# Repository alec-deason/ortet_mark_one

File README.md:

This is the electronics design and firmware for the Ortet Mark One MIDI controller.

## How to flash the firmware

In order to flash the firmware on the the controller's RP Pico you'll need to setup your rust environment by installing the `thumbv6m-none-eabi` target:
```
rustup target add thumbv6m-none-eabi
```

Then you will need `elf2uf2-rs` for building the UF2:
```
cargo install elf2uf2-rs
```

Then put the Pico into bootloader mode by holding the BOOTSEL button on the board while plugging it in to your computer. The board should mount as a USB drive at which point you can run:
```
cargo run --release
```

The project should build and install itself onto the Pico, then the Pico should reboot and present as a USB MIDI device named `Ortet MIDI Controller`.

For more information see the rp_pico documentation: https://github.com/rp-rs/rp-hal-boards/tree/main/boards/rp-pico

## License

This work is licensed under either of

- Apache License, Version 2.0 ([LICENSE-APACHE](LICENSE-APACHE) or
  <http://www.apache.org/licenses/LICENSE-2.0>)
- MIT license ([LICENSE-MIT](LICENSE-MIT) or <http://opensource.org/licenses/MIT>)

at your option.

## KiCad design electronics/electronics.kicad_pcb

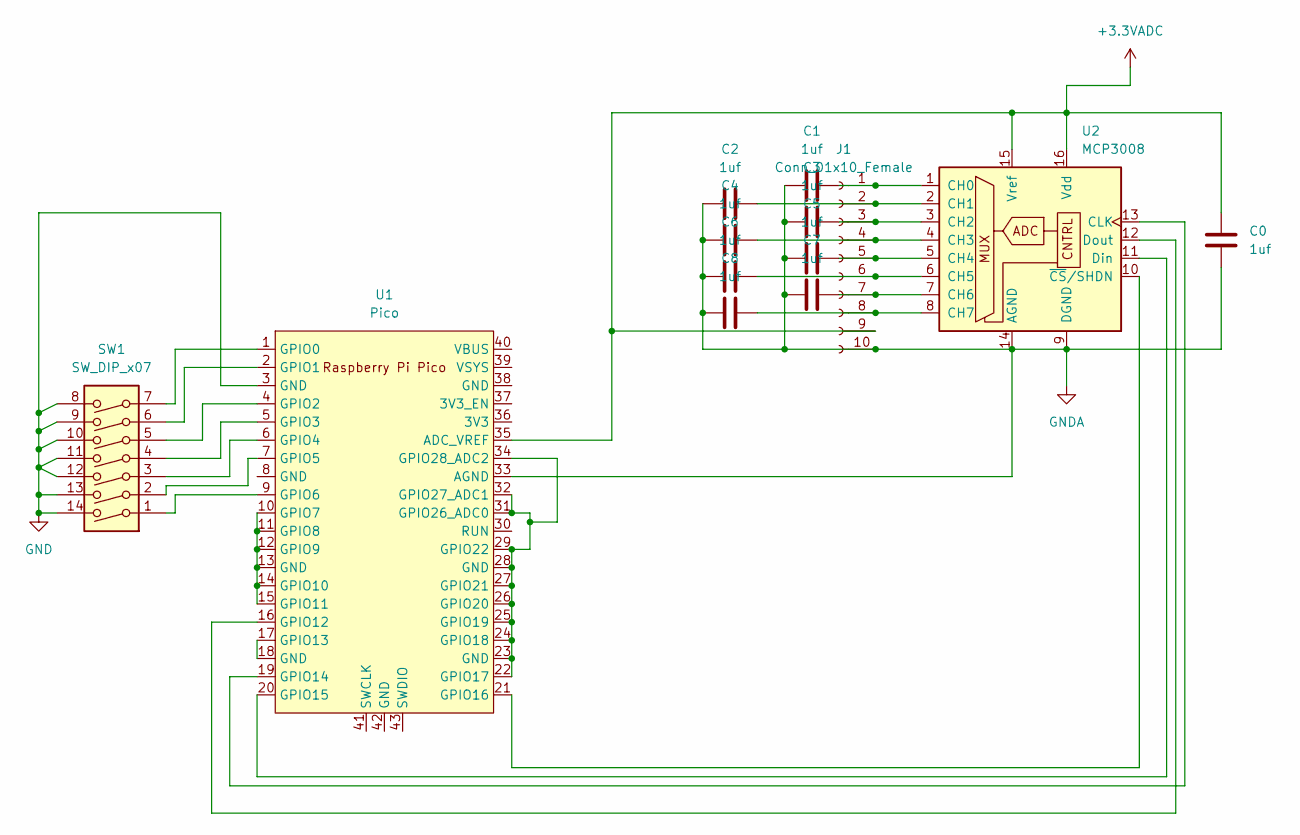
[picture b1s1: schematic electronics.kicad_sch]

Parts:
C0, C1, C2, C3, C4, C5, C6, C7, C8: 1uf; C_0603_1608Metric
J1: Conn_01x10_Female; PinHeader_2x05_P2.54mm_Vertical_SMD
SW1: SW_DIP_x07; DIP-14_W7.62mm_SMDSocket_SmallPads
U1: Pico; RPi_Pico_SMD_TH
U2: MCP3008; SOIC-16_3.9x9.9mm_P1.27mm

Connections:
+3.3VADC: C0.1, J1.9, U1.35 (ADC_VREF), U2.15 (Vref), U2.16 (Vdd)
GND: SW1.8, SW1.9, SW1.10, SW1.11, SW1.12, SW1.13, SW1.14, U1.3 (GND)
GNDA: C0.2, C1.1, C2.1, C3.1, C4.1, C5.1, C6.1, C7.1, C8.1, J1.10, U1.33 (AGND), U2.9 (DGND), U2.14 (AGND)
unnamed: C1.2, J1.1, U2.1 (CH0)
unnamed: C2.2, J1.2, U2.2 (CH1)
unnamed: C3.2, J1.3, U2.3 (CH2)
unnamed: C4.2, J1.4, U2.4 (CH3)
unnamed: C5.2, J1.5, U2.5 (CH4)
unnamed: C6.2, J1.6, U2.6 (CH5)
unnamed: C7.2, J1.7, U2.7 (CH6)
unnamed: C8.2, J1.8, U2.8 (CH7)
unnamed: SW1.1, U1.9 (GPIO6)
unnamed: SW1.2, U1.7 (GPIO5)
unnamed: SW1.3, U1.6 (GPIO4)
unnamed: SW1.4, U1.5 (GPIO3)
unnamed: SW1.5, U1.4 (GPIO2)
unnamed: SW1.6, U1.2 (GPIO1)
unnamed: SW1.7, U1.1 (GPIO0)
unnamed: U1.10 (GPIO7), U1.11 (GPIO8), U1.12 (GPIO9), U1.13 (GND), U1.14 (GPIO10), U1.15 (GPIO11)
unnamed: U1.16 (GPIO12), U2.12 (Dout)
unnamed: U1.17 (GPIO13), U1.18 (GND)
unnamed: U1.19 (GPIO14), U2.13 (CLK)
unnamed: U1.20 (GPIO15), U2.11 (Din)
unnamed: U1.21 (GPIO16), U2.10 (~CS/SHDN)
unnamed: U1.22 (GPIO17), U1.23 (GND), U1.24 (GPIO18), U1.25 (GPIO19), U1.26 (GPIO20), U1.27 (GPIO21), U1.28 (GND), U1.29 (GPIO22), U1.31 (GPIO26_ADC0), U1.32 (GPIO27_ADC1), U1.34 (GPIO28_ADC2)

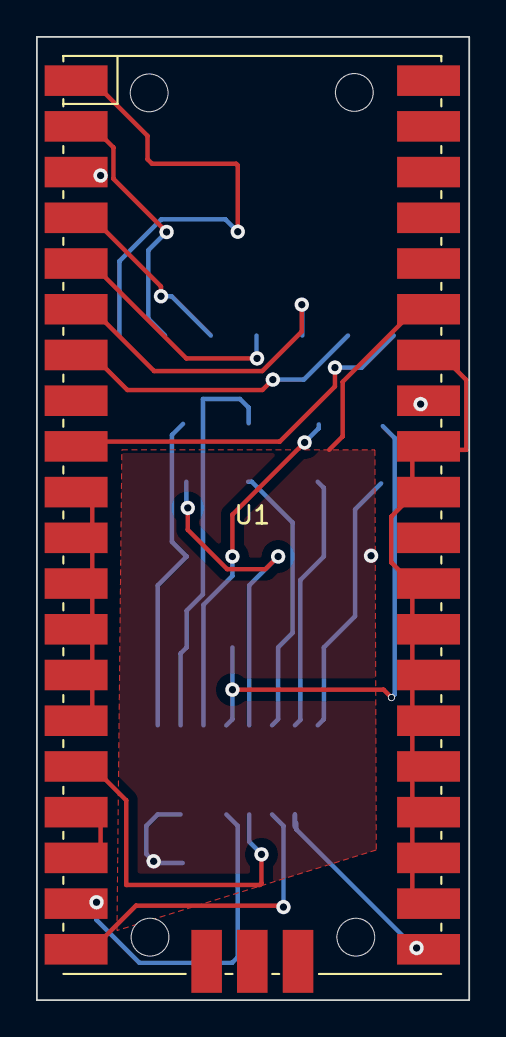
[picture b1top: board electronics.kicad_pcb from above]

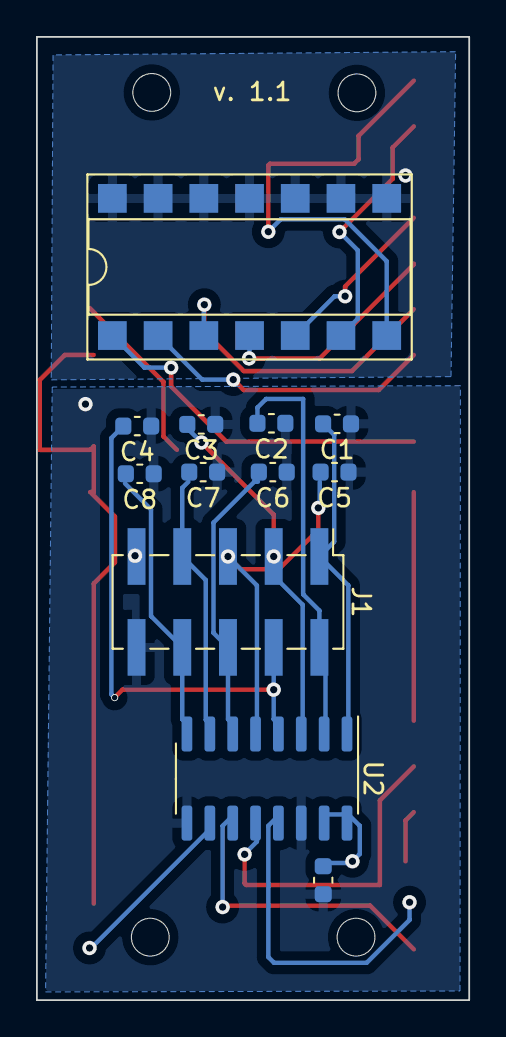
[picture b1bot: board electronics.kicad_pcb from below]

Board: 2 copper layers, 24.0 x 53.5 mm, 13 parts (12 on the bottom side), 25 nets.

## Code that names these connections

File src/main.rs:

//! Firmware for the Ortet Mark One series of midi controllers.

#![deny(warnings)]
#![no_std]
#![no_main]

use adc_mcp3008::Mcp3008;
use embedded_hal::digital::v2::{InputPin, OutputPin};
use fugit::RateExtU32;
use panic_halt as _;
use rp2040_hal::usb::UsbBus;
use rp_pico::entry;
use rp_pico::hal::{self, gpio::pin::bank0::Gpio16, pac, prelude::*};
use usb_device::{class_prelude::UsbBusAllocator, device::UsbVidPid, prelude::UsbDeviceBuilder};
use usbd_midi::{
    data::{
        byte::{from_traits::FromClamped, u7::U7},
        midi::{
            channel::Channel,
            message::{control_function::ControlFunction, Message},
        },
        usb::constants::USB_AUDIO_CLASS,
        usb_midi::{cable_number::CableNumber, usb_midi_event_packet::UsbMidiEventPacket},
    },
    midi_device::MidiClass,
};

type SPI = rp2040_hal::Spi<rp2040_hal::spi::Enabled, pac::SPI1, 8>;
type CS = rp2040_hal::gpio::Pin<Gpio16, rp2040_hal::gpio::Output<rp2040_hal::gpio::PushPull>>;

struct Controller {
    knob_values: [[u8; 2]; 8],

    midi_channel: Channel,
}

impl Controller {
    fn new(midi_channel: Channel) -> Self {
        Controller {
            knob_values: [[0,0]; 8],
            midi_channel,
        }
    }

    fn process_knobs(&mut self, adc: &mut Mcp3008<SPI, CS>, midi: &mut MidiClass<UsbBus>) -> Result<(), ()> {
        for i in 0..4 {
            let channel = match i {
                0 => adc_mcp3008::Channels8::CH0,
                1 => adc_mcp3008::Channels8::CH1,
                2 => adc_mcp3008::Channels8::CH2,
                3 => adc_mcp3008::Channels8::CH3,
                4 => adc_mcp3008::Channels8::CH4,
                5 => adc_mcp3008::Channels8::CH5,
                6 => adc_mcp3008::Channels8::CH6,
                7 => adc_mcp3008::Channels8::CH7,
                _ => unreachable!(),
            };
            let r = adc.read_channel(channel).map_err(|_| ())?;
            let r1 = (r / 8) as u8;
            if r1 != self.knob_values[i][0] && r1 != self.knob_values[i][1] {
                // We keep two samples worth of history here because sometimes there is just enough noise
                // to cause the value to bounce repeatedly between two adjacent values and we want to
                // suppress that without reducing over all sensitivity.
                self.knob_values[i][1] = self.knob_values[i][0];
                self.knob_values[i][0] = r1;
                let midi_message = UsbMidiEventPacket::from_midi(
                    CableNumber::Cable0,
                    Message::ControlChange(
                        self.midi_channel,
                        ControlFunction(U7::from_clamped(i as u8)),
                        U7::from_clamped(r1),
                    ),
                );
                midi.send_message(midi_message).map_err(|_| ())?;
            }
        }
        Ok(())
    }

    fn process(&mut self, adc: &mut Mcp3008<SPI, CS>, midi: &mut MidiClass<UsbBus>) -> Result<(), ()> {
        self.process_knobs(adc, midi)
    }
}

#[entry]
fn main() -> ! {
    let mut pac = pac::Peripherals::take().unwrap();
    let core = pac::CorePeripherals::take().unwrap();

    let mut watchdog = hal::Watchdog::new(pac.WATCHDOG);

    let clocks = hal::clocks::init_clocks_and_plls(
        rp_pico::XOSC_CRYSTAL_FREQ,
        pac.XOSC,
        pac.CLOCKS,
        pac.PLL_SYS,
        pac.PLL_USB,
        &mut pac.RESETS,
        &mut watchdog,
    )
    .ok()
    .unwrap();
    let mut delay = cortex_m::delay::Delay::new(core.SYST, clocks.system_clock.freq().to_Hz());

    let sio = hal::Sio::new(pac.SIO);

    let pins = rp_pico::Pins::new(
        pac.IO_BANK0,
        pac.PADS_BANK0,
        sio.gpio_bank0,
        &mut pac.RESETS,
    );

    let usb_bus = UsbBusAllocator::new(hal::usb::UsbBus::new(
        pac.USBCTRL_REGS,
        pac.USBCTRL_DPRAM,
        clocks.usb_clock,
        true,
        &mut pac.RESETS,
    ));

    let mut midi = MidiClass::new(&usb_bus, 1, 0).unwrap();

    let mut usb_dev = UsbDeviceBuilder::new(&usb_bus, UsbVidPid(0x16c0, 0x5e4))
        .product("Ortet MIDI Controller")
        .device_class(USB_AUDIO_CLASS)
        .build();

    let _spi_sclk = pins.gpio14.into_mode::<hal::gpio::FunctionSpi>();
    let _spi_mosi = pins.gpio15.into_mode::<hal::gpio::FunctionSpi>();
    let _spi_miso = pins.gpio12.into_mode::<hal::gpio::FunctionSpi>();
    let chip_enable = pins.gpio16.into_push_pull_output();

    let spi = hal::Spi::<_, _, 8>::new(pac.SPI1);
    let spi = spi.init(
        &mut pac.RESETS,
        clocks.peripheral_clock.freq(),
        1.MHz(),
        &adc_mcp3008::MODE,
    );
    let mut adc = adc_mcp3008::Mcp3008::new(spi, chip_enable).unwrap();

    let mut channel = 0;
    channel += pins.gpio6.into_pull_up_input().is_low().unwrap() as u8;
    channel += pins.gpio5.into_pull_up_input().is_low().unwrap() as u8 * 2;
    channel += pins.gpio4.into_pull_up_input().is_low().unwrap() as u8 * 4;
    channel += pins.gpio3.into_pull_up_input().is_low().unwrap() as u8 * 8;
    channel += pins.gpio2.into_pull_up_input().is_low().unwrap() as u8 * 16;
    channel += pins.gpio1.into_pull_up_input().is_low().unwrap() as u8 * 32;
    channel += pins.gpio0.into_pull_up_input().is_low().unwrap() as u8 * 64;
    let midi_channel = Channel::try_from(channel.min(15)).unwrap_or(Channel::Channel1);

    let mut controller = Controller::new(midi_channel);

    let mut led_pin = pins.led.into_push_pull_output();
    let _ = led_pin.set_high();

    loop {
        usb_dev.poll(&mut [&mut midi]);
        if controller.process(&mut adc, &mut midi).is_err() {
            let _ = led_pin.set_low();
            delay.delay_ms(100);
            let _ = led_pin.set_high();
        }
        delay.delay_ms(1);
    }
}

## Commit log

2023-01-27 Correct capacitor values
2023-01-28 Put delay between note on and note off events so they register
2023-05-10 Get ready to publish
2023-05-10 Fiddle the documentation
2023-05-10 Add repo
